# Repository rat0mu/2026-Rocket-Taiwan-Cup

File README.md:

# 2026 Rocket Taiwan Cup - Avionics System

## Overview
This repository contains the avionics system for our 2026 Rocket Taiwan Cup project.

The system is designed with a modular and fault-tolerant architecture, including:
- Dual flight computer (Primary + Secondary)
- Real-time state estimation
- Telemetry communication
- Data logging and post-flight analysis
- Safety-critical parachute deployment system

## System Architecture
The avionics system is divided into several major components:

- **Primary Flight Computer (PFC)**  
  Handles main flight logic, sensor fusion, and telemetry.

- **Secondary Flight Computer (SFC)**  
  Backup system for redundancy and failover.

- **Ground Station**  
  Receives telemetry and monitors mission status.

- **Simulation**  
  Used for testing flight dynamics and sensor models.

## Project Structure
```text
2026-Rocket-Taiwan-Cup/
├── firmware/          # Embedded flight software
├── hardware/          # PCB and electronics design
├── ground-station/    # Telemetry receiver and UI
├── simulation/        # Flight simulation and models
├── test/              # Unit / integration / HIL testing
├── docs/              # System documentation
└── tools/             # Development utilities
```

## Key Features
- Telemetry system (LoRa / RF communication)
- GPS-based positioning
- Sensor fusion (IMU + Barometer + GPS)
- Fail-safe parachute deployment
- State machine-based flight logic
- Onboard data logging

## Hardware
The hardware design includes multiple PCB layers:

- Avionics upper layer
- Middle layer
- Payload layer
- Lower layer

All PCB designs are located in `hardware/pcb/`.

## Testing Strategy
- Unit testing (algorithm-level)
- Integration testing (module-level)
- HIL (Hardware-in-the-loop)
- Simulation-based validation

## Communication
The system uses a custom telemetry protocol for:

- Sensor data transmission
- Flight state updates
- Command handling

See `docs/communication_protocol.md`.

## Flight States
The system operates using a state machine:

- Idle
- Launch Detection
- Ascent
- Apogee Detection
- Descent
- Recovery

See `docs/flight_state_machine.md`.

## Future Work
- Advanced navigation algorithm
- Improved fault detection
- Ground station UI enhancement
- Flight data visualization tools
- 
## License
MIT License

---

# 2026 火箭台灣盃 - 航電系統

## 專案總覽
本儲存庫包含我們 2026 火箭台灣盃專案的航電系統。

本系統採用模組化且具備容錯能力的架構設計，包含：
- 雙飛行電腦（主飛控 + 備援飛控）
- 即時狀態估測
- 遙測通訊
- 資料記錄與飛行後分析
- 安全關鍵的降落傘部署系統

## 系統架構
航電系統可分為以下幾個主要組成部分：

- **主飛行電腦（PFC）**  
  負責主要飛行邏輯、感測器融合與遙測通訊。

- **次飛行電腦（SFC）**  
  作為備援系統，提供冗餘與故障切換能力。

- **地面站**  
  接收遙測資料並監控任務狀態。

- **模擬系統**  
  用於測試飛行動力學與感測器模型。

## 專案結構
```text
2026-Rocket-Taiwan-Cup/
├── firmware/          # 嵌入式飛行軟體
├── hardware/          # PCB 與電子硬體設計
├── ground-station/    # 遙測接收與使用者介面
├── simulation/        # 飛行模擬與模型
├── test/              # 單元 / 整合 / HIL 測試
├── docs/              # 系統文件
└── tools/             # 開發工具
```

## 核心功能
- 遙測系統（LoRa / RF 通訊）
- 以 GPS 為基礎的定位能力
- 感測器融合（IMU + 氣壓計 + GPS）
- 故障保護式降落傘部署
- 以狀態機為基礎的飛行邏輯
- 機載資料記錄

## 硬體設計
硬體設計包含多個 PCB 層板：

- 航電上層
- 中層
- 酬載層
- 下層

所有 PCB 設計檔皆位於 `hardware/pcb/`。

## 測試策略
- 單元測試（演算法層級）
- 整合測試（模組層級）
- HIL（硬體迴圈測試）
- 基於模擬的驗證

## 通訊
本系統使用自訂遙測協定，負責：

- 感測器資料傳輸
- 飛行狀態更新
- 指令處理

請參閱 `docs/communication_protocol.md`。

## 飛行狀態
本系統以狀態機方式運作，包含以下狀態：

- Idle（待機）
- Launch Detection（發射偵測）
- Ascent（上升）
- Apogee Detection（最高點偵測）
- Descent（下降）
- Recovery（回收）

請參閱 `docs/flight_state_machine.md`。

## 未來工作
- 進階導航演算法
- 改善故障偵測能力
- 強化地面站 UI
- 飛行資料視覺化工具

## 授權
MIT License

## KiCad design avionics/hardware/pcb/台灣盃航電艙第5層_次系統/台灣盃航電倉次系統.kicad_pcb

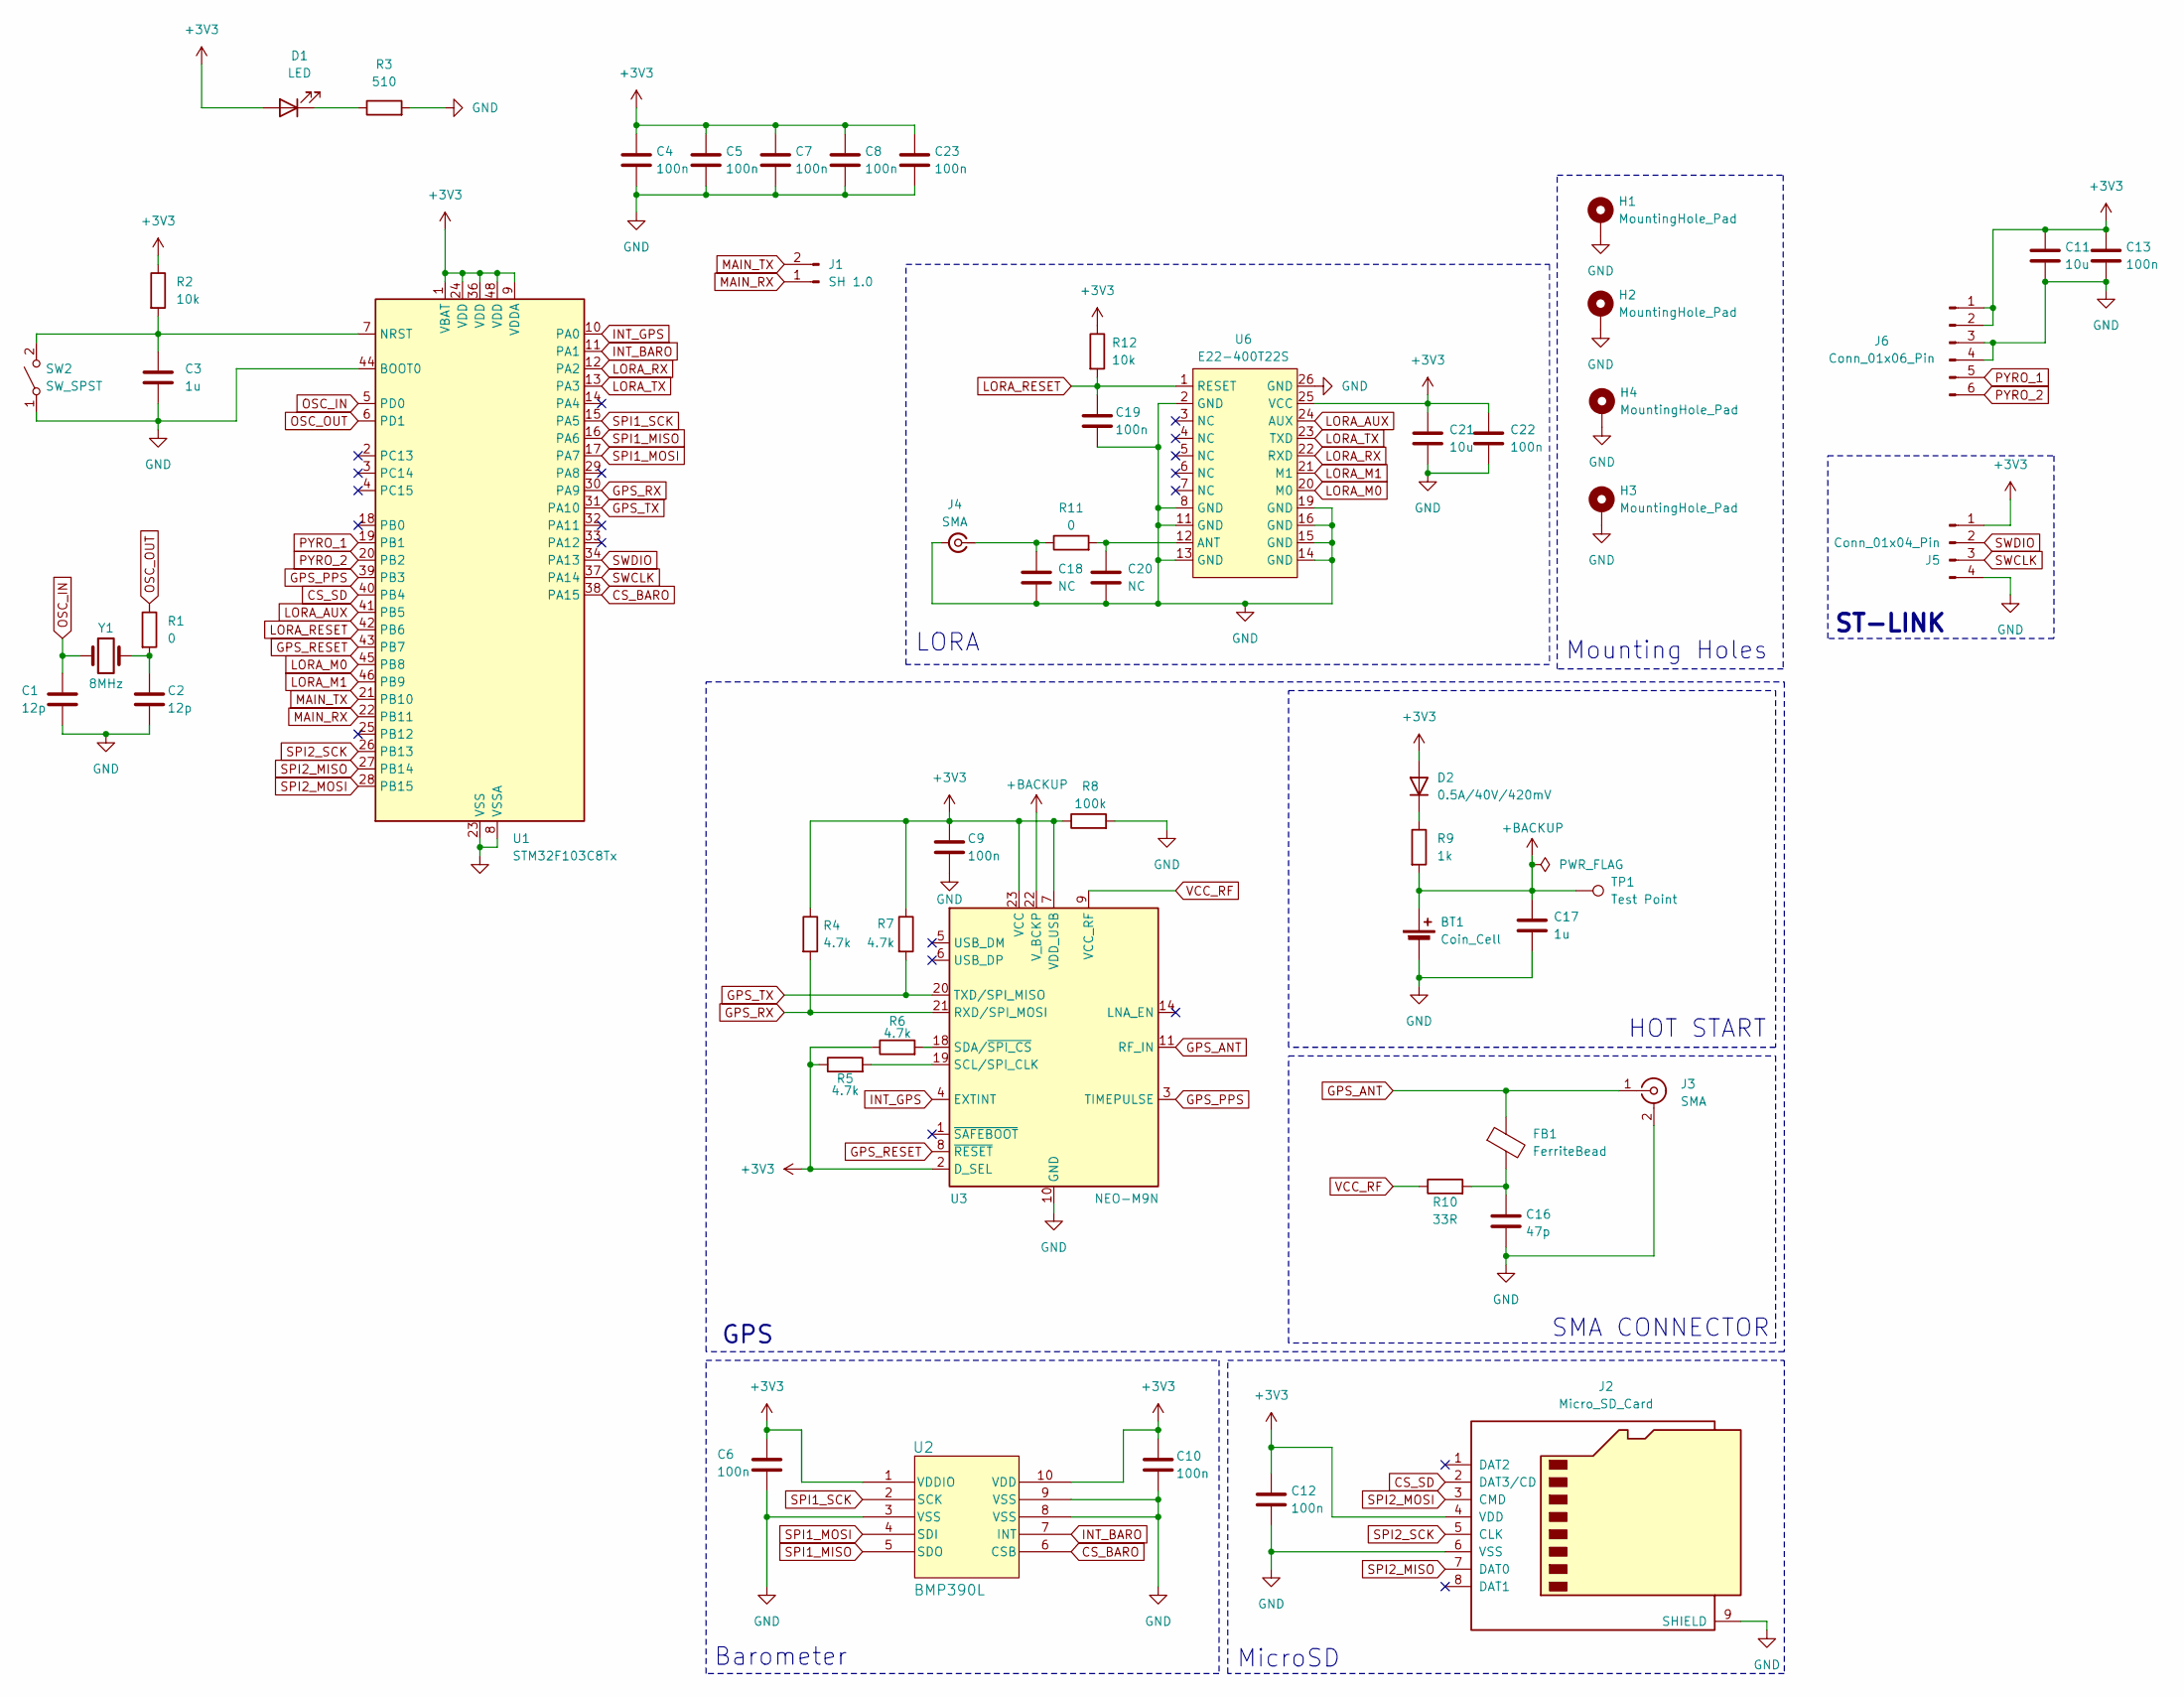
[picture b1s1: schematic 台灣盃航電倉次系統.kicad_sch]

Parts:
BT1: Coin_Cell; BatteryHolder_Keystone_3000_1x12mm
C1, C2: 12p; C_0201_0603Metric
C3: 1u; C_0603_1608Metric
C4, C5, C7, C8, C23: 100n; C_0402_1005Metric
C6, C10, C12, C13, C19, C22: 100n; C_0603_1608Metric
C9: 100n; C_0201_0603Metric
C11: 10u; C_0603_1608Metric
C16: 47p; C_0201_0603Metric
C17: 1u; C_0201_0603Metric
C18, C20: NC; C_0402_1005Metric
C21: 10u; C_0805_2012Metric
D1: LED; LED_0201_0603Metric
D2: 0.5A/40V/420mV; D_SOD-123
FB1: FerriteBead; L_0603_1608Metric
H1, H2, H3, H4: MountingHole_Pad; MountingHole_3.2mm_M3_ISO14580_Pad
J1: SH 1.0; JST_XH_S2B-XH-A_1x02_P2.50mm_Horizontal
J2: Micro_SD_Card; microSD_HC_Hirose_DM3D-SF
J3, J4: SMA; SMA_Amphenol_132134-11_Vertical
J5: Conn_01x04_Pin; PinHeader_1x04_P2.54mm_Horizontal
J6: Conn_01x06_Pin; JST_XH_S6B-XH-A_1x06_P2.50mm_Horizontal
R1: 0; R_0603_1608Metric
R2, R12: 10k; R_0603_1608Metric
R3: 510; R_0603_1608Metric
R4, R5, R6, R7: 4.7k; R_0603_1608Metric
R8: 100k; R_0603_1608Metric
R9: 1k; R_0603_1608Metric
R10: 33R; R_0603_1608Metric
R11: 0; R_0402_1005Metric
SW2: SW_SPST; SW_SPST_FSMSM
TP1: Test Point; TestPoint_Pad_1.0x1.0mm
U1: STM32F103C8Tx; LQFP-48_7x7mm_P0.5mm
U2: BMP390L; XDCR_BMP390L
U3: NEO-M9N; ublox_NEO
U6: E22-400T22S; PE22-230T22S
Y1: 8MHz; Crystal_SMD_3225-4Pin_3.2x2.5mm

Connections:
+3V3: C4.1, C5.1, C6.1, C7.1, C8.1, C9.1, C10.1, C11.1, C12.1, C13.1, C21.1, C22.1, C23.1, D1.2 (A), D2.2 (A), J2.4 (VDD), J5.1, J6.1, J6.2, R2.1, R4.1, R5.1, R6.1, R7.1, R8.1, R12.1, U1.1 (VBAT), U1.9 (VDDA), U1.24 (VDD), U1.36 (VDD), U1.48 (VDD), U2.1 (VDDIO), U2.10 (VDD), U3.2 (D_SEL), U3.7 (VDD_USB), U3.23 (VCC), U6.25 (VCC)
+BACKUP: BT1.1 (+), C17.1, R9.2, TP1.1, U3.22 (V_BCKP)
CS_BARO: U1.38 (PA15), U2.6 (CSB)
CS_SD: J2.2 (DAT3/CD), U1.40 (PB4)
GND: BT1.2 (-), C1.2, C2.2, C3.2, C4.2, C5.2, C6.2, C7.2, C8.2, C9.2, C10.2, C11.2, C12.2, C13.2, C16.2, C17.2, C18.2, C19.2, C20.2, C21.2, C22.2, C23.2, H1.1, H2.1, H3.1, H4.1, J2.6 (VSS), J2.9 (SHIELD), J3.2 (Ext), J4.2 (Ext), J5.4, J6.3, J6.4, R3.2, R8.2, SW2.1 (A), U1.8 (VSSA), U1.23 (VSS), U1.35 (VSS), U1.44 (BOOT0), U1.47 (VSS), U2.3 (VSS), U2.8 (VSS), U2.9 (VSS), U3.10 (GND), U3.12 (GND), U3.13 (GND), U3.24 (GND), U6.2 (GND), U6.8 (GND), U6.11 (GND), U6.13 (GND), U6.14 (GND), U6.15 (GND), U6.16 (GND), U6.19 (GND), U6.26 (GND)
GPS_ANT: FB1.1, J3.1 (In), U3.11 (RF_IN)
GPS_PPS: U1.39 (PB3), U3.3 (TIMEPULSE)
GPS_RESET: U1.43 (PB7), U3.8 (~RESET)
GPS_RX: R4.2, U1.30 (PA9), U3.21 (RXD/SPI_MOSI)
GPS_TX: R7.2, U1.31 (PA10), U3.20 (TXD/SPI_MISO)
INT_BARO: U1.11 (PA1), U2.7 (INT)
INT_GPS: U1.10 (PA0), U3.4 (EXTINT)
LORA_AUX: U1.41 (PB5), U6.24 (AUX)
LORA_M0: U1.45 (PB8), U6.20 (M0)
LORA_M1: U1.46 (PB9), U6.21 (M1)
LORA_RESET: C19.1, R12.2, U1.42 (PB6), U6.1 (RESET)
LORA_RX: U1.12 (PA2), U6.22 (RXD)
LORA_TX: U1.13 (PA3), U6.23 (TXD)
MAIN_RX: J1.1, U1.22 (PB11)
MAIN_TX: J1.2, U1.21 (PB10)
unnamed: C2.1, R1.2, Y1.2
unnamed: C16.1, FB1.2, R10.2
unnamed: D1.1 (K), R3.1
unnamed: D2.1 (K), R9.1
unnamed: C18.1, J4.1 (In), R11.1
unnamed: C3.1, R2.2, SW2.2 (B), U1.7 (NRST)
unnamed: R5.2, U3.19 (SCL/SPI_CLK)
unnamed: R6.2, U3.18 (SDA/~SPI_CS)
unnamed: C20.1, R11.2, U6.12 (ANT)
OSC_IN: C1.1, U1.5 (PD0), Y1.1
OSC_OUT: R1.1, U1.6 (PD1)
PYRO_1: J6.5, U1.19 (PB1)
PYRO_2: J6.6, U1.20 (PB2)
SPI1_MISO: U1.16 (PA6), U2.5 (SDO)
SPI1_MOSI: U1.17 (PA7), U2.4 (SDI)
SPI1_SCK: U1.15 (PA5), U2.2 (SCK)
SPI2_MISO: J2.7 (DAT0), U1.27 (PB14)
SPI2_MOSI: J2.3 (CMD), U1.28 (PB15)
SPI2_SCK: J2.5 (CLK), U1.26 (PB13)
SWCLK: J5.3, U1.37 (PA14)
SWDIO: J5.2, U1.34 (PA13)
VCC_RF: R10.1, U3.9 (VCC_RF)

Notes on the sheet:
MicroSD
GPS
SMA CONNECTOR
Barometer
Mounting Holes
HOT START
LORA
ST-LINK

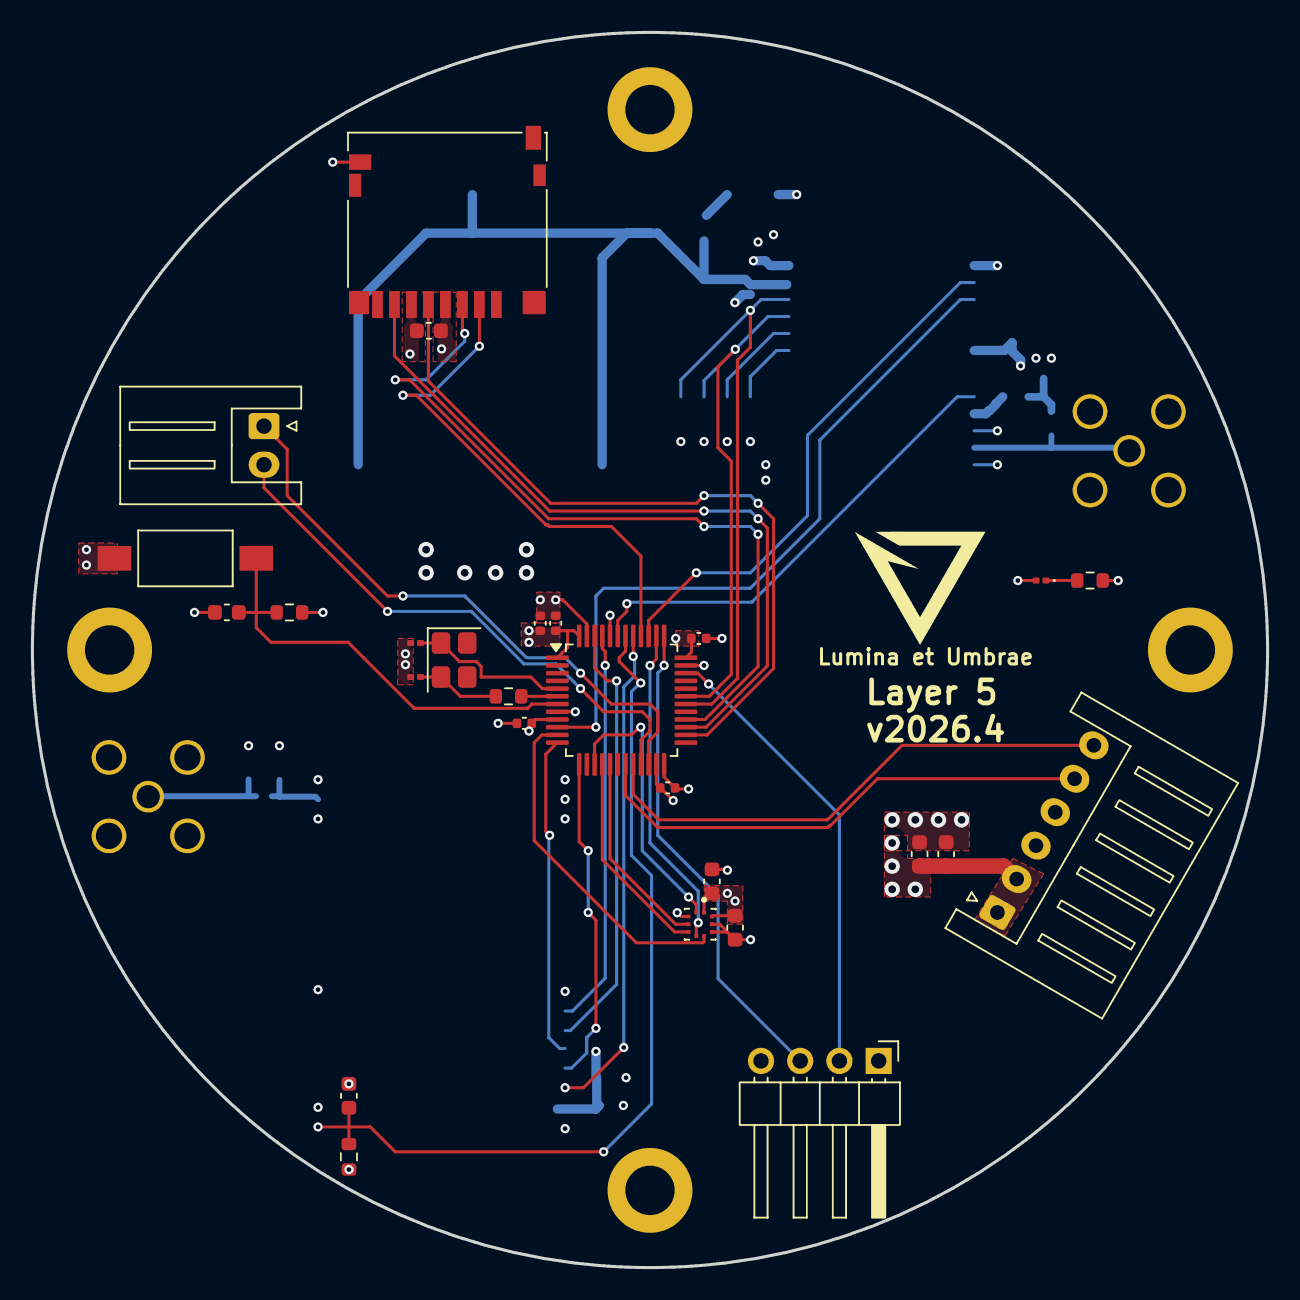
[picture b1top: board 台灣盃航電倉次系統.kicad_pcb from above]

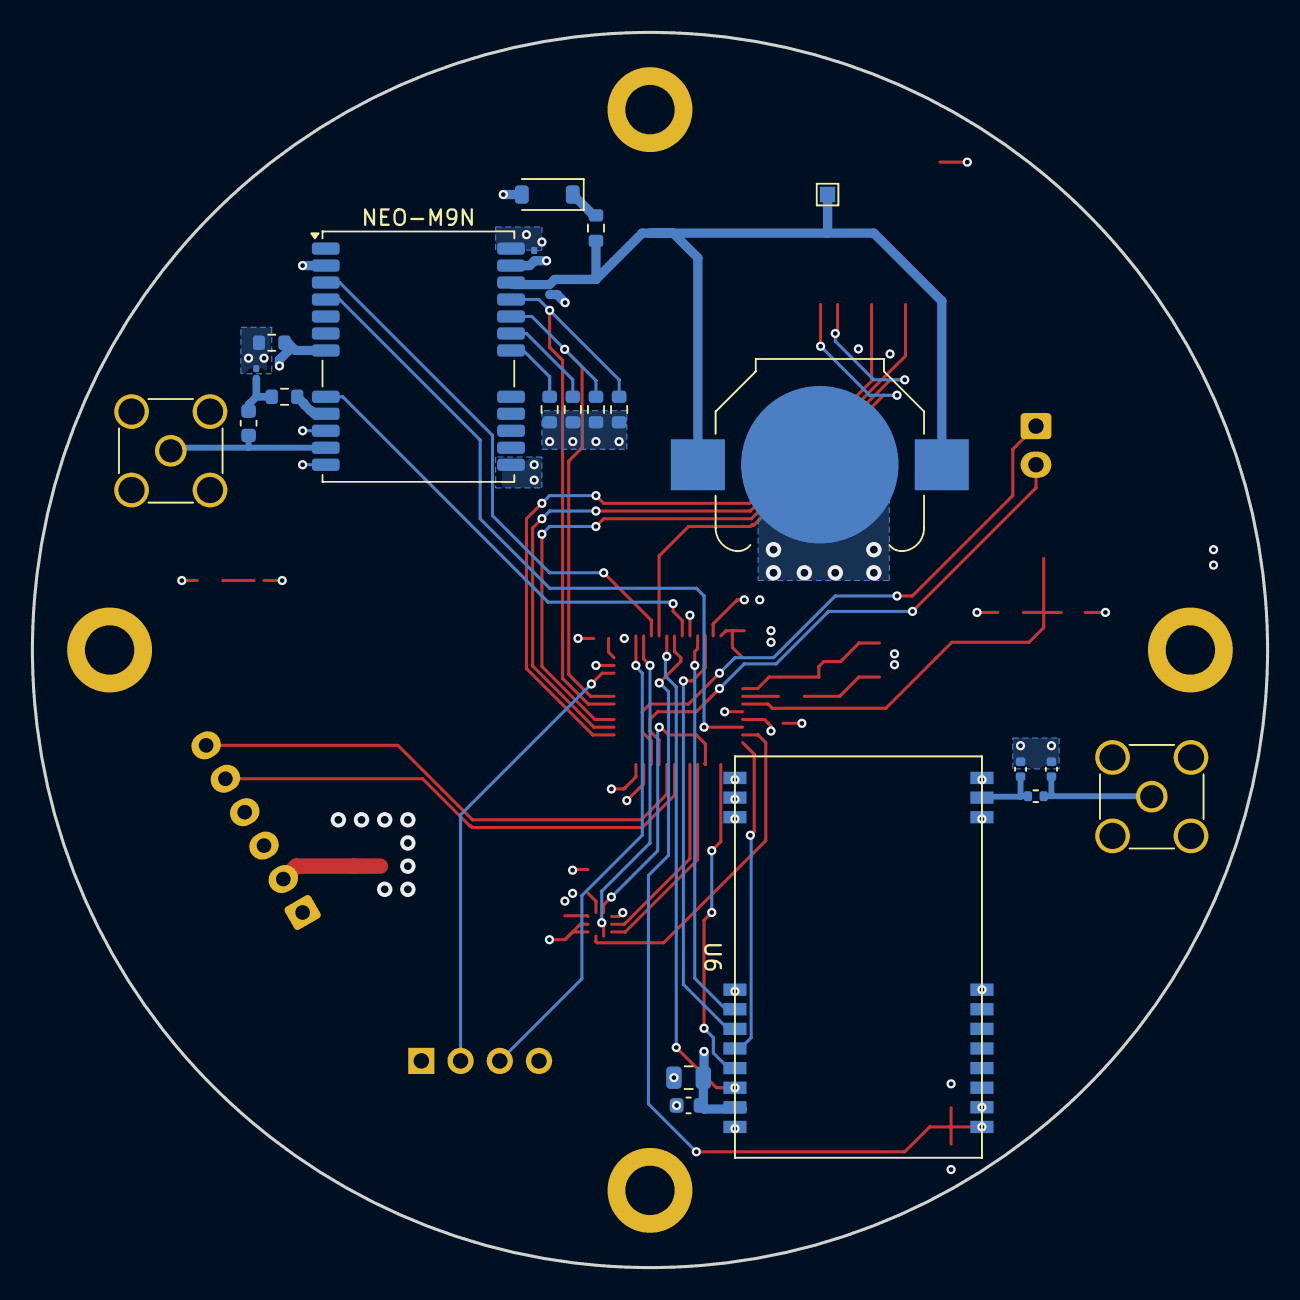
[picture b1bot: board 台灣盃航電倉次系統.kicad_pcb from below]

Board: 4 copper layers, 80.0 x 80.0 mm, 54 parts (23 on the bottom side), 42 nets.

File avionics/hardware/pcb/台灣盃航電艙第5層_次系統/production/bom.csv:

Designator,Footprint,Quantity,Value,LCSC Part #
BT1,BatteryHolder_Keystone_3000_1x12mm,1,Coin_Cell,
"C1, C2",0201,2,12p,
"C10, C12, C13, C19, C22, C6",0603,6,100n,
C11,0603,1,10u,
C16,0201,1,47p,
C17,0201,1,1u,
"C18, C20",0402,2,NC,
C21,0805,1,10u,
"C23, C4, C5, C7, C8",0402,5,100n,
C3,0603,1,1u,
C9,0201,1,100n,
D1,0201,1,LED,
D2,D_SOD-123,1,0.5A/40V/420mV,
FB1,0603,1,FerriteBead,
J1,JST_XH_S2B-XH-A_1x02_P2.50mm_Horizontal,1,SH 1.0,
J2,microSD_HC_Hirose_DM3D-SF,1,Micro_SD_Card,
"J3, J4",SMA_Amphenol_132134-11_Vertical,2,SMA,
J5,PinHeader_1x04_P2.54mm_Horizontal,1,Conn_01x04_Pin,
J6,JST_XH_S6B-XH-A_1x06_P2.50mm_Horizontal,1,Conn_01x06_Pin,
R1,0603,1,0,
R10,0603,1,33R,
R11,0402,1,0,
"R12, R2",0603,2,10k,
R3,0603,1,510,
"R4, R5, R6, R7",0603,4,4.7k,
R8,0603,1,100k,
R9,0603,1,1k,
SW2,SW_SPST_FSMSM,1,SW_SPST,
TP1,TestPoint_Pad_1.0x1.0mm,1,Test Point,
U1,LQFP-48_7x7mm_P0.5mm,1,STM32F103C8Tx,
U2,XDCR_BMP390L,1,BMP390L,
U3,ublox_NEO,1,NEO-M9N,
U6,PE22-230T22S,1,E22-400T22S,
Y1,Crystal_SMD_3225-4Pin_3.2x2.5mm,1,8MHz,

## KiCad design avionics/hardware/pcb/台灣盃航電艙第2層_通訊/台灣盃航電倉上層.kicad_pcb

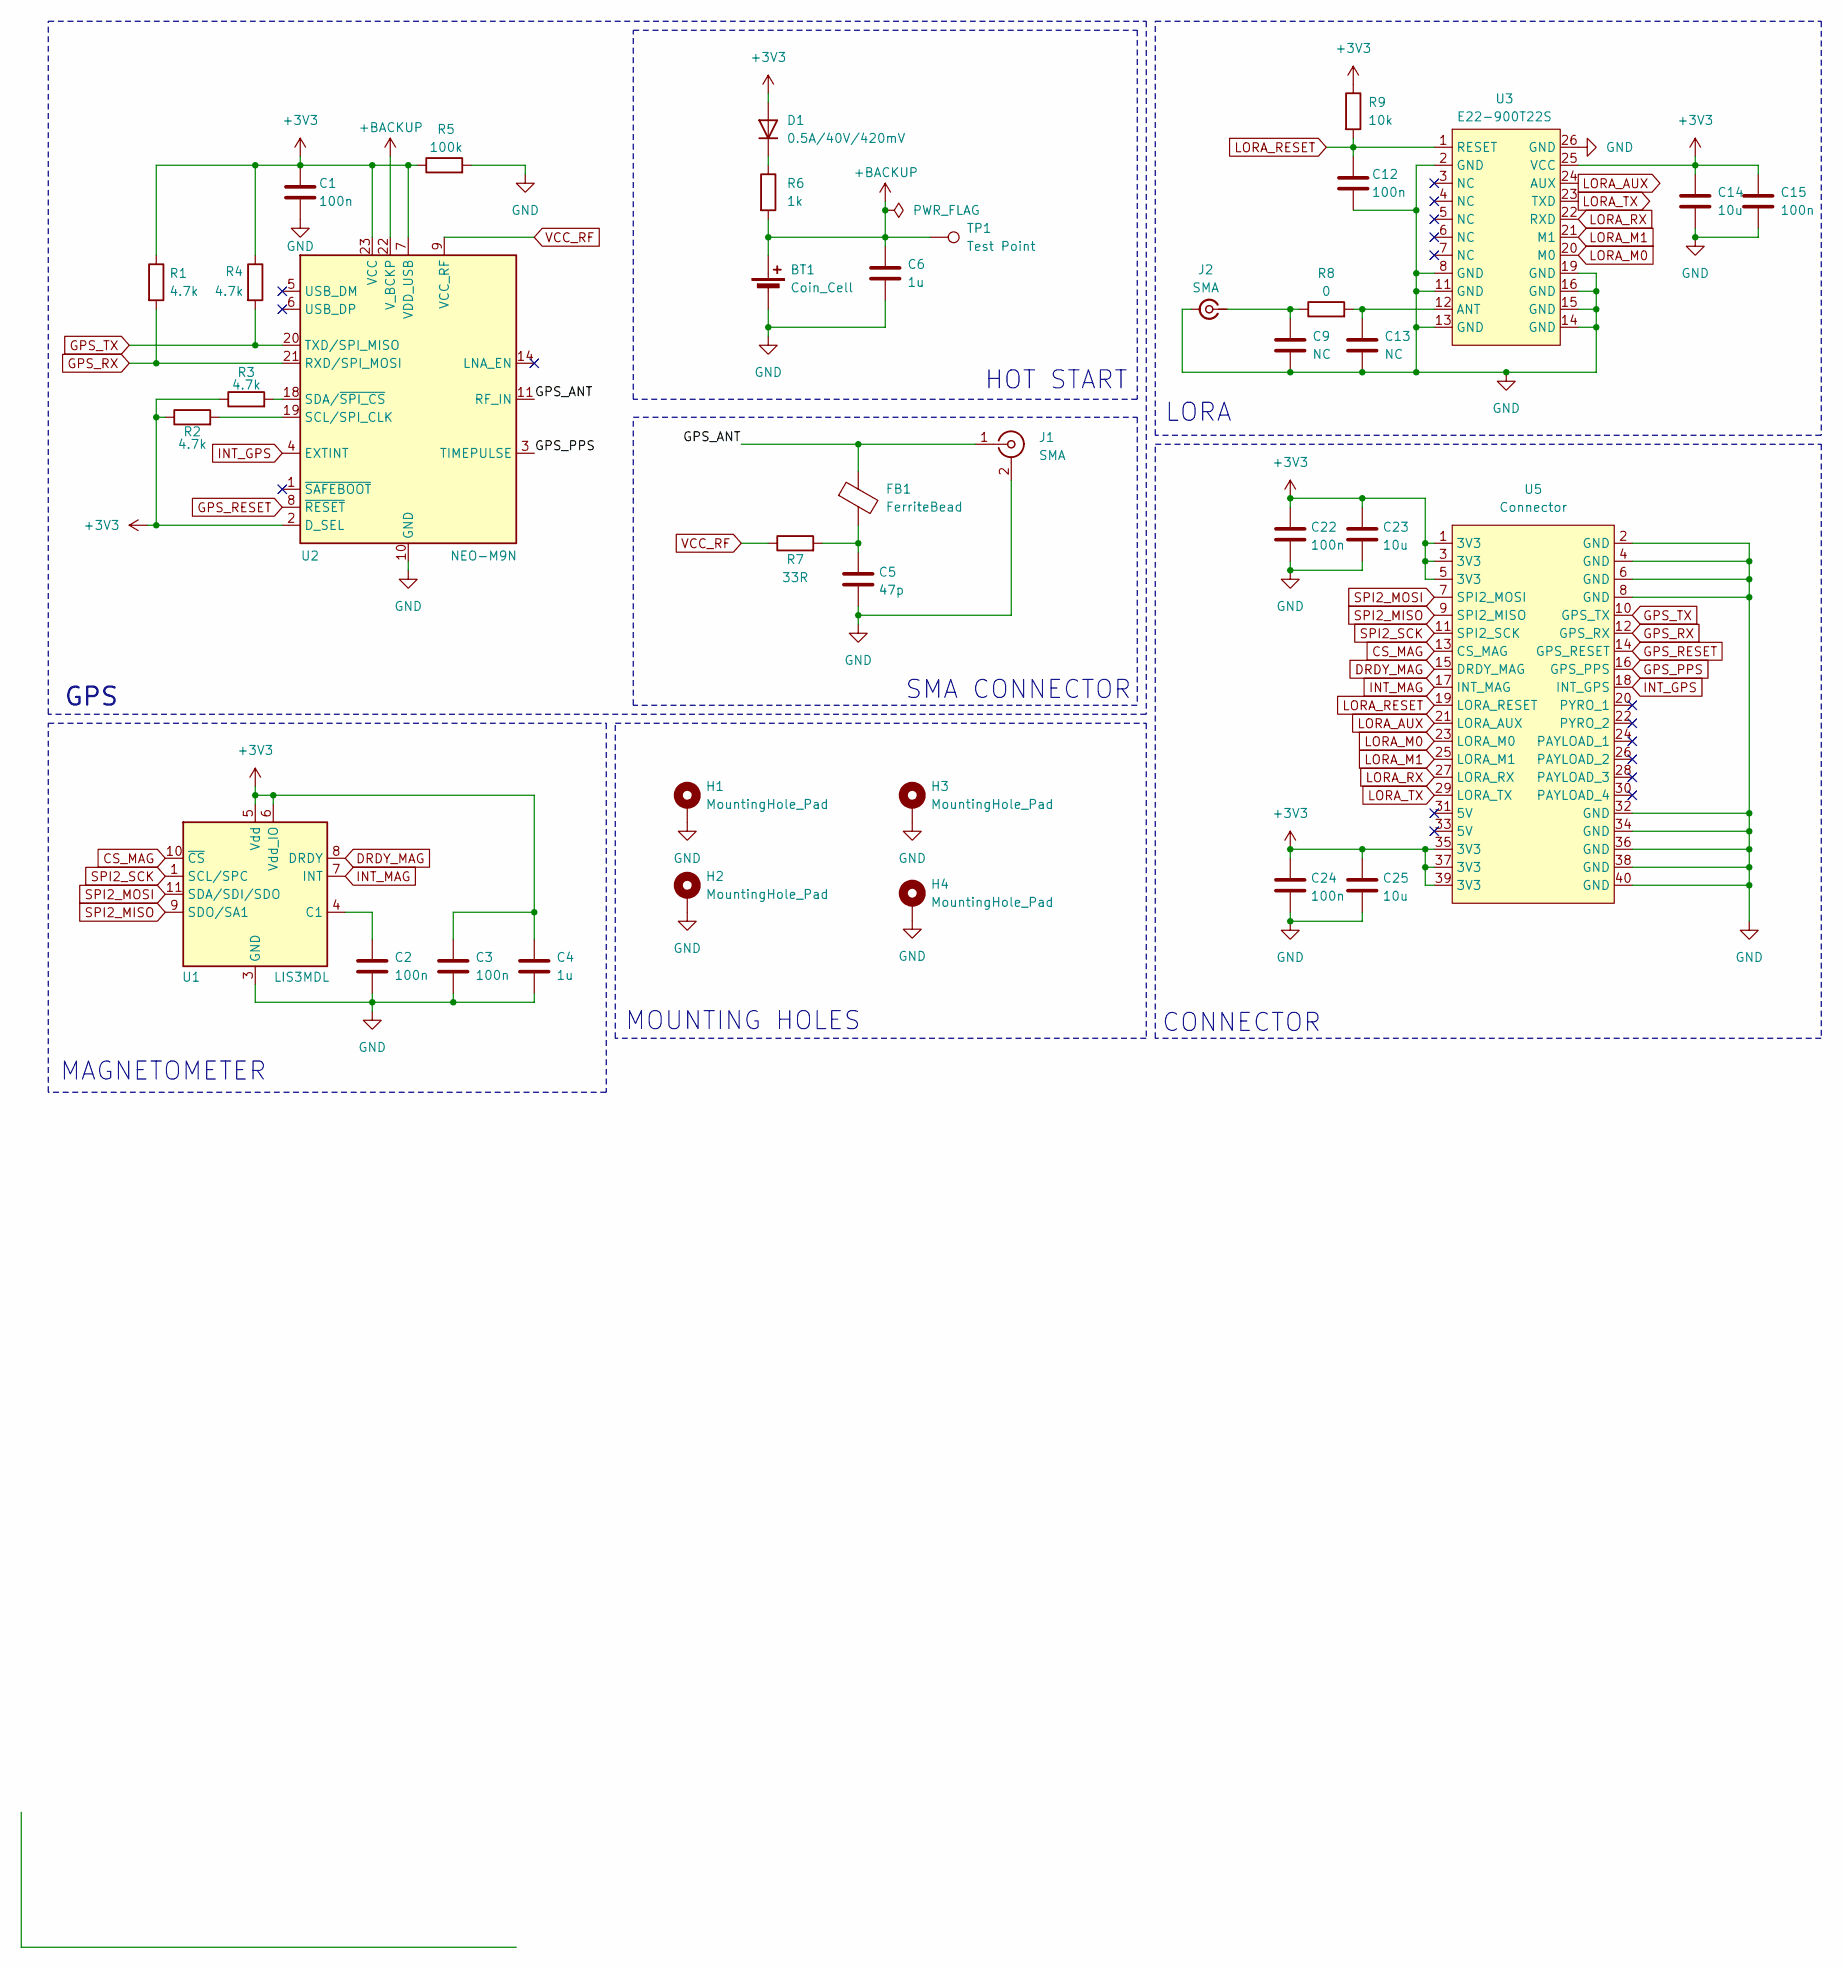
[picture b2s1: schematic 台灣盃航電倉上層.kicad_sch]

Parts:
BT1: Coin_Cell; BatteryHolder_Keystone_3000_1x12mm
C1: 100n; C_0201_0603Metric
C2, C3, C12, C15: 100n; C_0603_1608Metric
C4: 1u; C_0603_1608Metric
C5: 47p; C_0201_0603Metric
C6: 1u; C_0201_0603Metric
C9, C13: NC; C_0402_1005Metric
C14: 10u; C_0805_2012Metric
C22, C24: 100n; C_0402_1005Metric
C23, C25: 10u; C_0603_1608Metric
D1: 0.5A/40V/420mV; D_SOD-123
FB1: FerriteBead; L_0603_1608Metric
H1, H2, H3, H4: MountingHole_Pad; MountingHole_2.2mm_M2_DIN965_Pad
J1, J2: SMA; SMA_Amphenol_132134-11_Vertical
R1, R2, R3, R4: 4.7k; R_0603_1608Metric
R5: 100k; R_0603_1608Metric
R6: 1k; R_0603_1608Metric
R7: 33R; R_0603_1608Metric
R8: 0; R_0402_1005Metric
R9: 10k; R_0603_1608Metric
TP1: Test Point; TestPoint_Pad_1.0x1.0mm
U1: LIS3MDL; LGA-12_2x2mm_P0.5mm
U2: NEO-M9N; ublox_NEO
U3: E22-900T22S; PE22-230T22S
U5: Connector; PinHeader_2x20_P2.54mm_Vertical

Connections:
+3V3: C1.1, C3.1, C4.1, C14.1, C15.1, C22.1, C23.1, C24.1, C25.1, D1.2 (A), R1.1, R2.1, R3.1, R4.1, R5.1, R9.1, U1.5 (Vdd), U1.6 (Vdd_IO), U2.2 (D_SEL), U2.7 (VDD_USB), U2.23 (VCC), U3.25 (VCC), U5.1 (3V3), U5.3 (3V3), U5.5 (3V3), U5.35 (3V3), U5.37 (3V3), U5.39 (3V3)
+BACKUP: BT1.1 (+), C6.1, R6.2, TP1.1, U2.22 (V_BCKP)
/GPS_ANT: FB1.1, J1.1 (In), U2.11 (RF_IN)
CS_MAG: U1.10 (~CS), U5.13 (CS_MAG)
DRDY_MAG: U1.8 (DRDY), U5.15 (DRDY_MAG)
GND: BT1.2 (-), C1.2, C2.2, C3.2, C4.2, C5.2, C6.2, C9.2, C12.2, C13.2, C14.2, C15.2, C22.2, C23.2, C24.2, C25.2, H1.1, H2.1, H3.1, H4.1, J1.2 (Ext), J2.2 (Ext), R5.2, U1.2 (GND), U1.3 (GND), U1.12 (GND), U2.10 (GND), U2.12 (GND), U2.13 (GND), U2.24 (GND), U3.2 (GND), U3.8 (GND), U3.11 (GND), U3.13 (GND), U3.14 (GND), U3.15 (GND), U3.16 (GND), U3.19 (GND), U3.26 (GND), U5.2 (GND), U5.4 (GND), U5.6 (GND), U5.8 (GND), U5.32 (GND), U5.34 (GND), U5.36 (GND), U5.38 (GND), U5.40 (GND)
GPS_PPS: U2.3 (TIMEPULSE), U5.16 (GPS_PPS)
GPS_RESET: U2.8 (~RESET), U5.14 (GPS_RESET)
GPS_RX: R1.2, U2.21 (RXD/SPI_MOSI), U5.12 (GPS_RX)
GPS_TX: R4.2, U2.20 (TXD/SPI_MISO), U5.10 (GPS_TX)
INT_GPS: U2.4 (EXTINT), U5.18 (INT_GPS)
INT_MAG: U1.7 (INT), U5.17 (INT_MAG)
LORA_AUX: U3.24 (AUX), U5.21 (LORA_AUX)
LORA_M0: U3.20 (M0), U5.23 (LORA_M0)
LORA_M1: U3.21 (M1), U5.25 (LORA_M1)
LORA_RESET: C12.1, R9.2, U3.1 (RESET), U5.19 (LORA_RESET)
LORA_RX: U3.22 (RXD), U5.27 (LORA_RX)
LORA_TX: U3.23 (TXD), U5.29 (LORA_TX)
unnamed: C5.1, FB1.2, R7.2
unnamed: D1.1 (K), R6.1
unnamed: C9.1, J2.1 (In), R8.1
unnamed: C2.1, U1.4 (C1)
unnamed: R2.2, U2.19 (SCL/SPI_CLK)
unnamed: R3.2, U2.18 (SDA/~SPI_CS)
unnamed: C13.1, R8.2, U3.12 (ANT)
SPI2_MISO: U1.9 (SDO/SA1), U5.9 (SPI2_MISO)
SPI2_MOSI: U1.11 (SDA/SDI/SDO), U5.7 (SPI2_MOSI)
SPI2_SCK: U1.1 (SCL/SPC), U5.11 (SPI2_SCK)
VCC_RF: R7.1, U2.9 (VCC_RF)

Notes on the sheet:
HOT START
MAGNETOMETER
GPS
MOUNTING HOLES
LORA
SMA CONNECTOR
CONNECTOR

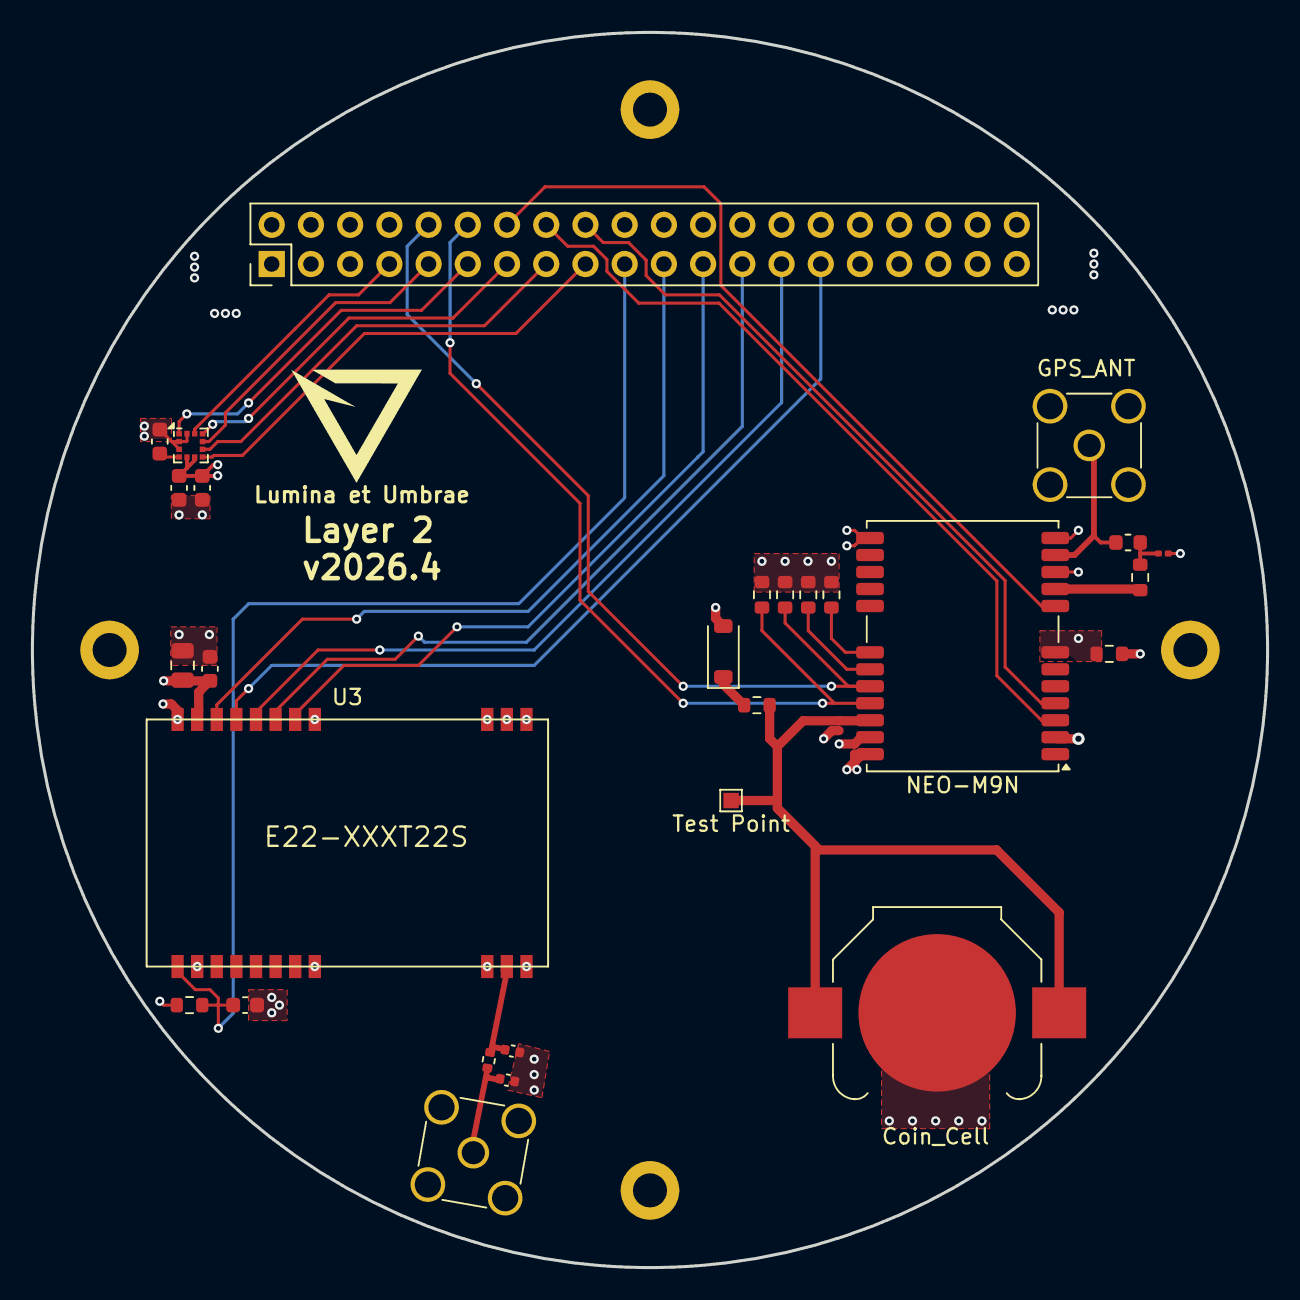
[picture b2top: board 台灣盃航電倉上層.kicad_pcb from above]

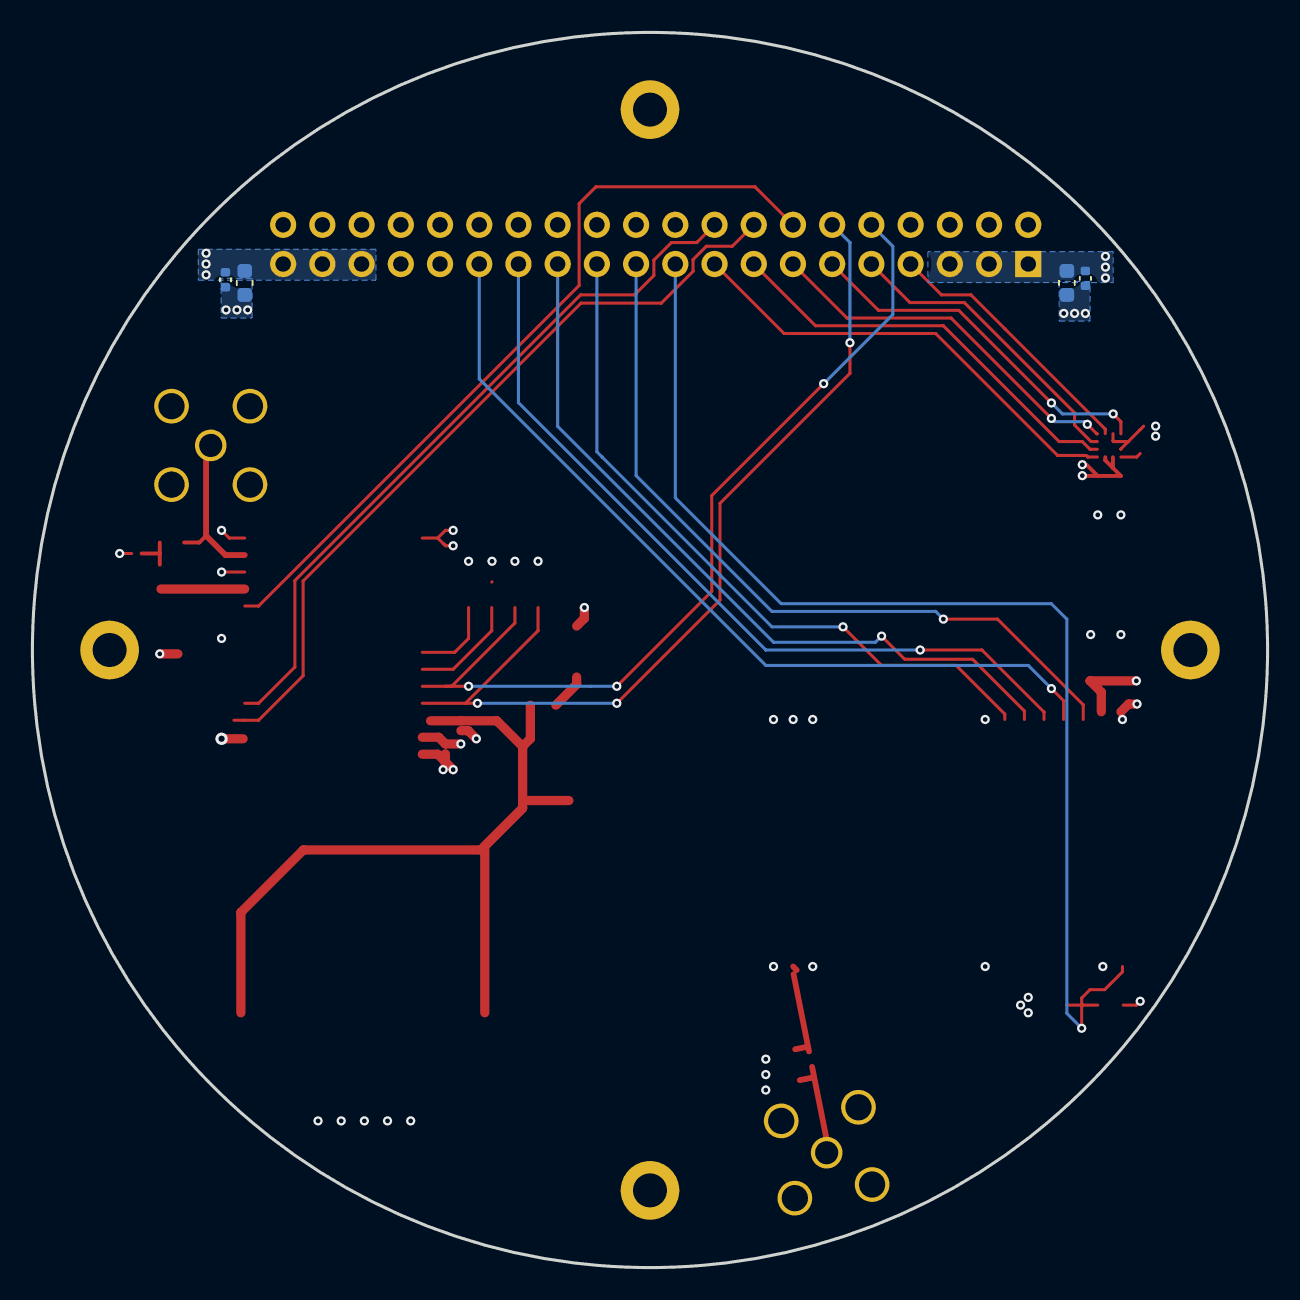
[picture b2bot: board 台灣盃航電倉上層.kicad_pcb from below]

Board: 4 copper layers, 80.0 x 80.0 mm, 38 parts (4 on the bottom side), 29 nets.

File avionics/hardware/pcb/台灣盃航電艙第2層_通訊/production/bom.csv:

Designator,Footprint,Quantity,Value,LCSC Part #
BT1,BatteryHolder_Keystone_3000_1x12mm,1,Coin_Cell,
C1,0201,1,100n,
"C12, C15, C2, C3",0603,4,100n,
"C13, C9",0402,2,NC,
C14,0805,1,10u,
"C22, C24",0402,2,100n,
"C23, C25",0603,2,10u,
C4,0603,1,1u,
C5,0201,1,47p,
C6,0201,1,1u,
D1,D_SOD-123,1,0.5A/40V/420mV,
FB1,0603,1,FerriteBead,
"J1, J2",SMA_Amphenol_132134-11_Vertical,2,SMA,
"R1, R2, R3, R4",0603,4,4.7k,
R5,0603,1,100k,
R6,0603,1,1k,
R7,0603,1,33R,
R8,0402,1,0,
R9,0603,1,10k,
TP1,TestPoint_Pad_1.0x1.0mm,1,Test Point,
U1,LGA-12_2x2mm_P0.5mm,1,LIS3MDL,
U2,ublox_NEO,1,NEO-M9N,
U3,PE22-230T22S,1,E22-900T22S,
U5,PinHeader_2x20_P2.54mm_Vertical,1,Connector,
